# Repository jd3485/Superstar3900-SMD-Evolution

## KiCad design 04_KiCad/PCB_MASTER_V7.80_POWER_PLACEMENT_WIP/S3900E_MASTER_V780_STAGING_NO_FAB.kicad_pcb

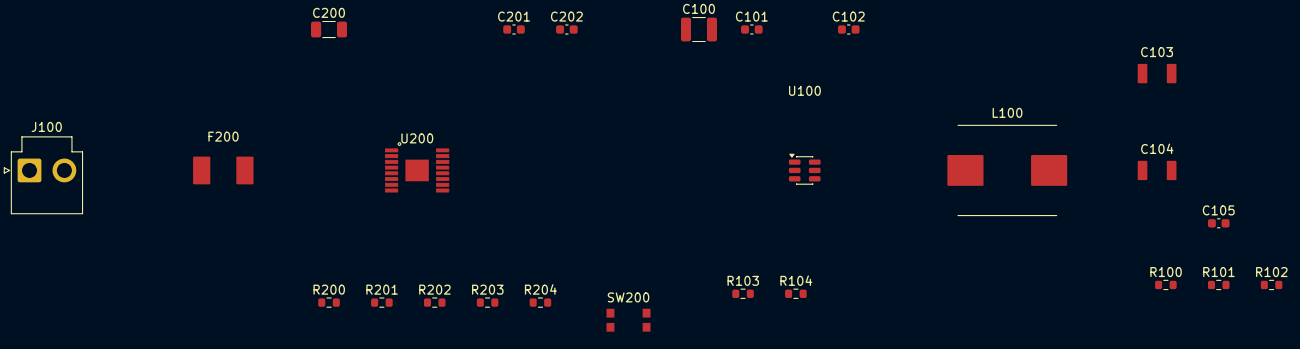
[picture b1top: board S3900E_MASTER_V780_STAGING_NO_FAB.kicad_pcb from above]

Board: 2 copper layers, 25 parts (0 on the bottom side), 17 nets, no tracks yet.

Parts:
C100: 10uF 35V X7R; C_1210_3225Metric
C101: 100nF 50V X7R; C_0603_1608Metric
C102: 100nF 25V X7R; C_0603_1608Metric
C103, C104: 22uF 25V X7R; TDK_CGA6_1210_AECQ200_C103_C104_VENDOR_LAND_HOLD
C105: 75pF 50V C0G; C_0603_1608Metric
C200: 100nF 100V X7R; C_1206_3216Metric
C201: 22nF 50V X7R; C_0603_1608Metric
C202: 1uF 35V X7R; C_0603_1608Metric
F200: 1.5A 045101.5MRL CANDIDATO; LF451_045101_5MRL_VENDOR_CANDIDATE
J100: INGRESSO_AUX_13V8_DRAFT; JST_VH_B2P-VH_1x02_P3.96mm_Vertical
L100: 15uH SRP1038A-150M; SRP1038A_150M_BOURNS_VENDOR_CANDIDATE
R100: 49R9 1%; R_0603_1608Metric
R101: 100k 1%; R_0603_1608Metric
R102: 13k3 1%; R_0603_1608Metric
R103: 510k 5%; R_0603_1608Metric
R104: 105k 1%; R_0603_1608Metric
R200: 365k 1%; R_0603_1608Metric
R201: 16k2 1%; R_0603_1608Metric
R202: 30k1 1%; R_0603_1608Metric
R203: 8k2 1%; R_0603_1608Metric
R204: 402k 1% MODE_LATCHOFF_CANDIDATE; R_0603_1608Metric
SW200: KMR223NG ULC LFG (CANDIDATE); CK_KMR223NG_ULC_LFG_4PAD_VENDOR_LAND_REVIEW
U100: TPS54202DDCR; SOT-23-6
U200: TPS26600PWPT; TPS26600_PWP0016H_EXAMPLE_LAND_REVIEW

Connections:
/AUX_POWER_existing_V1_5_UNQUALIFIED/01 PROTEZIONE AUX/BUCK_VIN_PROTECTED: C100.2, C101.2, C202.2, R103.2, U100.3, U200.15, U200.16
/AUX_POWER_existing_V1_5_UNQUALIFIED/01 PROTEZIONE AUX/DV_DT_NODE: C201.2, U200.12
/AUX_POWER_existing_V1_5_UNQUALIFIED/01 PROTEZIONE AUX/EFUSE_MODE: R204.2, U200.6
/AUX_POWER_existing_V1_5_UNQUALIFIED/01 PROTEZIONE AUX/EFUSE_RTN: C201.1, R202.1, R203.1, R204.1, U200.8, U200.17
/AUX_POWER_existing_V1_5_UNQUALIFIED/01 PROTEZIONE AUX/EFUSE_SHDN_RESET_N: SW200.1, SW200.4, U200.7
/AUX_POWER_existing_V1_5_UNQUALIFIED/01 PROTEZIONE AUX/EFUSE_VIN: C200.2, F200.2, R200.2, U200.1, U200.2
/AUX_POWER_existing_V1_5_UNQUALIFIED/01 PROTEZIONE AUX/ILIM_NODE: R203.2, U200.11
/AUX_POWER_existing_V1_5_UNQUALIFIED/01 PROTEZIONE AUX/OVP_NODE: R201.1, R202.2, U200.5
/AUX_POWER_existing_V1_5_UNQUALIFIED/01 PROTEZIONE AUX/UVLO_NODE: R200.1, R201.2, U200.3
/AUX_POWER_existing_V1_5_UNQUALIFIED/02 BUCK 5V/5V_RF_PREREGULATED: C103.2, C104.2, L100.2, R100.2
/AUX_POWER_existing_V1_5_UNQUALIFIED/02 BUCK 5V/BUCK_BOOT: C102.1, U100.6
/AUX_POWER_existing_V1_5_UNQUALIFIED/02 BUCK 5V/BUCK_DIV_TOP: C105.2, R100.1, R101.2
/AUX_POWER_existing_V1_5_UNQUALIFIED/02 BUCK 5V/BUCK_EN: R103.1, R104.2, U100.5
/AUX_POWER_existing_V1_5_UNQUALIFIED/02 BUCK 5V/BUCK_FB: C105.1, R101.1, R102.2, U100.4
/AUX_POWER_existing_V1_5_UNQUALIFIED/02 BUCK 5V/BUCK_SW: C102.2, L100.1, U100.2
/AUX_POWER_existing_V1_5_UNQUALIFIED/GND_MAIN: C100.1, C101.1, C103.1, C104.1, C200.1, C202.1, J100.2, R102.1, R104.1, SW200.2, SW200.3, U100.1, U200.9
/AUX_POWER_existing_V1_5_UNQUALIFIED/PWR_13V8_AUX_RAW: F200.1, J100.1

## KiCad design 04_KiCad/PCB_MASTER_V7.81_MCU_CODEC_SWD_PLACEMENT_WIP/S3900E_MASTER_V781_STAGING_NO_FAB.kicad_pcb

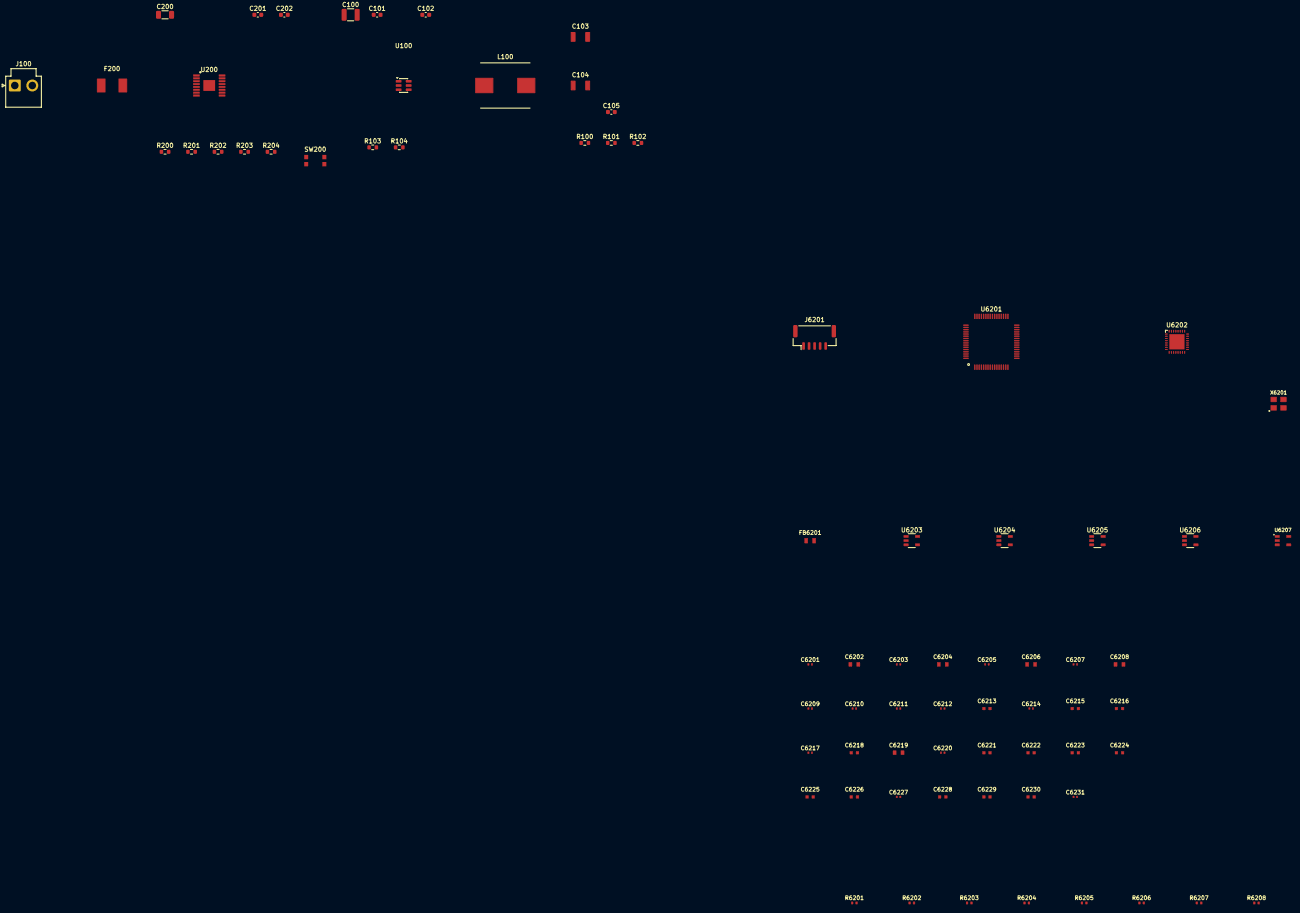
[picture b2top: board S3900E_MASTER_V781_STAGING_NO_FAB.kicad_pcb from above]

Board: 2 copper layers, 74 parts (0 on the bottom side), 46 nets, no tracks yet.

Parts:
C100: 10uF 35V X7R; C_1210_3225Metric
C101: 100nF 50V X7R; C_0603_1608Metric
C102: 100nF 25V X7R; C_0603_1608Metric
C103, C104: 22uF 25V X7R; TDK_CGA6_1210_AECQ200_C103_C104_VENDOR_LAND_HOLD
C105: 75pF 50V C0G; C_0603_1608Metric
C200: 100nF 100V X7R; C_1206_3216Metric
C201: 22nF 50V X7R; C_0603_1608Metric
C202: 1uF 35V X7R; C_0603_1608Metric
C6201, C6203, C6205, C6207, C6209, C6210, C6211, C6212, C6214, C6217, C6220, C6227, C6231: 100nF; MURATA_GRM15_0402_REFLOW_REVIEW
C6202, C6204, C6206, C6208, C6219: 10uF; TDK_C2012_0805_10UF_REFLOW_REVIEW
C6213, C6215, C6216, C6218, C6221, C6222, C6223, C6224, C6225, C6226, C6229: 1uF; TDK_C1608_0603_1UF_REFLOW_REVIEW
C6228: 4.7nF; TDK_C1608_0603_C0G_REFLOW_REVIEW
C6230: 10nF; TDK_C1608_0603_C0G_REFLOW_REVIEW
F200: 1.5A 045101.5MRL CANDIDATO; LF451_045101_5MRL_VENDOR_CANDIDATE
FB6201: 600R@100MHz_TDK_2A_REVIEW; TDK_MPZ2012_0805_POWER_BEAD_REFLOW_REVIEW
J100: INGRESSO_AUX_13V8_DRAFT; JST_VH_B2P-VH_1x02_P3.96mm_Vertical
J6201: BM05B-GHS-TBT(LF)(SN); JST_GH_BM05B-GHS-TBT_1x05-1MP_P1.25mm_Vertical
L100: 15uH SRP1038A-150M; SRP1038A_150M_BOURNS_VENDOR_CANDIDATE
R100: 49R9 1%; R_0603_1608Metric
R101: 100k 1%; R_0603_1608Metric
R102: 13k3 1%; R_0603_1608Metric
R103: 510k 5%; R_0603_1608Metric
R104: 105k 1%; R_0603_1608Metric
R200: 365k 1%; R_0603_1608Metric
R201: 16k2 1%; R_0603_1608Metric
R202: 30k1 1%; R_0603_1608Metric
R203: 8k2 1%; R_0603_1608Metric
R204: 402k 1% MODE_LATCHOFF_CANDIDATE; R_0603_1608Metric
R6201: 47k; YAGEO_RC0402_REFLOW_VENDOR_CANDIDATE
R6202, R6203, R6204, R6206: 4.7k; YAGEO_RC0402_REFLOW_VENDOR_CANDIDATE
R6205: 33R; YAGEO_RC0402_REFLOW_VENDOR_CANDIDATE
R6207, R6208: 1k; YAGEO_RC0402_REFLOW_VENDOR_CANDIDATE
SW200: KMR223NG ULC LFG (CANDIDATE); CK_KMR223NG_ULC_LFG_4PAD_VENDOR_LAND_REVIEW
U100: TPS54202DDCR; SOT-23-6
U200: TPS26600PWPT; TPS26600_PWP0016H_EXAMPLE_LAND_REVIEW
U6201: STM32G474RET6 (DRAFT); STM32G474RE_LQFP64_ST_DS12288_CANDIDATE
U6202: TLV320AIC3204 (DRAFT); TLV320AIC3204_RHB0032E_VENDOR_CANDIDATE
U6203, U6204, U6205, U6206: TPS7A2033PDBVR; TPS7A20_DBV0005A_VENDOR_CANDIDATE
U6207: TPS3840PL30DBVR; TI_DBV0005A_5PAD_REFLOW_REVIEW
X6201: SiT8008AI-22-33E-12.288000; SiT8008AI_3225_VENDOR_CANDIDATE

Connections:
/AUX_POWER_existing_V1_5_UNQUALIFIED/01 PROTEZIONE AUX/BUCK_VIN_PROTECTED: C100.2, C101.2, C202.2, R103.2, U100.3, U200.15, U200.16
/AUX_POWER_existing_V1_5_UNQUALIFIED/01 PROTEZIONE AUX/DV_DT_NODE: C201.2, U200.12
/AUX_POWER_existing_V1_5_UNQUALIFIED/01 PROTEZIONE AUX/EFUSE_MODE: R204.2, U200.6
/AUX_POWER_existing_V1_5_UNQUALIFIED/01 PROTEZIONE AUX/EFUSE_RTN: C201.1, R202.1, R203.1, R204.1, U200.8, U200.17
/AUX_POWER_existing_V1_5_UNQUALIFIED/01 PROTEZIONE AUX/EFUSE_SHDN_RESET_N: SW200.1, SW200.4, U200.7
/AUX_POWER_existing_V1_5_UNQUALIFIED/01 PROTEZIONE AUX/EFUSE_VIN: C200.2, F200.2, R200.2, U200.1, U200.2
/AUX_POWER_existing_V1_5_UNQUALIFIED/01 PROTEZIONE AUX/ILIM_NODE: R203.2, U200.11
/AUX_POWER_existing_V1_5_UNQUALIFIED/01 PROTEZIONE AUX/OVP_NODE: R201.1, R202.2, U200.5
/AUX_POWER_existing_V1_5_UNQUALIFIED/01 PROTEZIONE AUX/UVLO_NODE: R200.1, R201.2, U200.3
/AUX_POWER_existing_V1_5_UNQUALIFIED/02 BUCK 5V/5V_RF_PREREGULATED: C103.2, C104.2, L100.2, R100.2
/AUX_POWER_existing_V1_5_UNQUALIFIED/02 BUCK 5V/BUCK_BOOT: C102.1, U100.6
/AUX_POWER_existing_V1_5_UNQUALIFIED/02 BUCK 5V/BUCK_DIV_TOP: C105.2, R100.1, R101.2
/AUX_POWER_existing_V1_5_UNQUALIFIED/02 BUCK 5V/BUCK_EN: R103.1, R104.2, U100.5
/AUX_POWER_existing_V1_5_UNQUALIFIED/02 BUCK 5V/BUCK_FB: C105.1, R101.1, R102.2, U100.4
/AUX_POWER_existing_V1_5_UNQUALIFIED/02 BUCK 5V/BUCK_SW: C102.2, L100.1, U100.2
/AUX_POWER_existing_V1_5_UNQUALIFIED/GND_MAIN: C100.1, C101.1, C103.1, C104.1, C200.1, C202.1, J100.2, R102.1, R104.1, SW200.2, SW200.3, U100.1, U200.9
/AUX_POWER_existing_V1_5_UNQUALIFIED/PWR_13V8_AUX_RAW: F200.1, J100.1
/MCU_CODEC_AFE_existing_V2_1_UNQUALIFIED/3V3_ANA_MCU: C6214.1, U6201.28, U6201.29
/MCU_CODEC_AFE_existing_V2_1_UNQUALIFIED/3V3_AUDIO_CLK: C6216.1, C6217.1, C6218.1, R6204.1, U6203.5, X6201.4
/MCU_CODEC_AFE_existing_V2_1_UNQUALIFIED/3V3_CODEC_IO: C6201.1, C6224.1, C6231.1, R6202.2, R6203.2, R6206.1, U6202.6, U6205.5, U6207.2
/MCU_CODEC_AFE_existing_V2_1_UNQUALIFIED/3V3_CODEC_LDOIN: C6207.1, C6208.1, C6226.1, U6202.26, U6206.5
/MCU_CODEC_AFE_existing_V2_1_UNQUALIFIED/3V3_MCU: C6209.1, C6210.1, C6211.1, C6212.1, C6213.1, C6222.1, J6201.1, U6201.1, U6201.16, U6201.32, U6201.48, U6201.64, U6204.5
/MCU_CODEC_AFE_existing_V2_1_UNQUALIFIED/5V_DIGITAL_FILTERED: C6215.1, C6219.1, C6220.1, C6221.1, C6223.1, C6225.1, FB6201.2, U6203.1, U6203.3, U6204.1, U6204.3, U6205.1, U6205.3, U6206.1
/MCU_CODEC_AFE_existing_V2_1_UNQUALIFIED/AUDIO_BCLK: U6201.30, U6202.2
/MCU_CODEC_AFE_existing_V2_1_UNQUALIFIED/AUDIO_I2S_RX: U6201.58, U6202.5
/MCU_CODEC_AFE_existing_V2_1_UNQUALIFIED/AUDIO_I2S_TX: U6201.9, U6202.4
/MCU_CODEC_AFE_existing_V2_1_UNQUALIFIED/AUDIO_MCLK_12M288: R6205.2, U6202.1
/MCU_CODEC_AFE_existing_V2_1_UNQUALIFIED/AUDIO_WCLK: U6201.43, U6202.3
/MCU_CODEC_AFE_existing_V2_1_UNQUALIFIED/CODEC_AVDD_LDO_OUT: C6203.1, C6204.1, U6202.24
/MCU_CODEC_AFE_existing_V2_1_UNQUALIFIED/CODEC_DVDD_LDO_OUT: C6205.1, C6206.1, U6202.29
/MCU_CODEC_AFE_existing_V2_1_UNQUALIFIED/CODEC_I2C_SCL: R6202.1, U6201.59, U6202.9
/MCU_CODEC_AFE_existing_V2_1_UNQUALIFIED/CODEC_I2C_SDA: R6203.1, U6201.60, U6202.10
/MCU_CODEC_AFE_existing_V2_1_UNQUALIFIED/CODEC_LDOIN_EN_SUPERVISED: U6206.3, U6207.1
/MCU_CODEC_AFE_existing_V2_1_UNQUALIFIED/CODEC_LDO_SELECT: R6206.2, U6202.30
/MCU_CODEC_AFE_existing_V2_1_UNQUALIFIED/CODEC_REF: C6202.1, U6202.18
/MCU_CODEC_AFE_existing_V2_1_UNQUALIFIED/CODEC_RESET_N: R6201.1, U6201.10, U6202.31
/MCU_CODEC_AFE_existing_V2_1_UNQUALIFIED/FM_AC_COUPLED: C6229.2, R6208.1
/MCU_CODEC_AFE_existing_V2_1_UNQUALIFIED/FM_CODEC_IN: C6230.1, R6208.2, U6202.16
/MCU_CODEC_AFE_existing_V2_1_UNQUALIFIED/GND: C6201.2, C6202.2, C6203.2, C6204.2, C6205.2, C6206.2, C6207.2, C6208.2, C6209.2, C6210.2, C6211.2, C6212.2, C6213.2, C6214.2, C6215.2, C6216.2, C6217.2, C6218.2, C6219.2, C6220.2, C6221.2, C6222.2, C6223.2, C6224.2, C6225.2, C6226.2, C6228.2, C6230.2, C6231.2, J6201.5, R6201.2, U6201.15, U6201.27, U6201.31, U6201.47, U6201.63, U6202.7, U6202.12, U6202.17, U6202.28, U6202.33, U6203.2, U6204.2, U6205.2, U6206.2, U6207.3, X6201.2
/MCU_CODEC_AFE_existing_V2_1_UNQUALIFIED/MCU_NRST: J6201.4, U6201.7
/MCU_CODEC_AFE_existing_V2_1_UNQUALIFIED/MCU_SWCLK: J6201.3, U6201.50
/MCU_CODEC_AFE_existing_V2_1_UNQUALIFIED/MCU_SWDIO: J6201.2, U6201.49
/MCU_CODEC_AFE_existing_V2_1_UNQUALIFIED/MIC_AC_COUPLED: C6227.2, R6207.1
/MCU_CODEC_AFE_existing_V2_1_UNQUALIFIED/MIC_CODEC_IN: C6228.1, R6207.2, U6202.13
/MCU_CODEC_AFE_existing_V2_1_UNQUALIFIED/XO_MCLK_RAW: R6205.1, X6201.3
/MCU_CODEC_AFE_existing_V2_1_UNQUALIFIED/XO_OE: R6204.2, X6201.1
